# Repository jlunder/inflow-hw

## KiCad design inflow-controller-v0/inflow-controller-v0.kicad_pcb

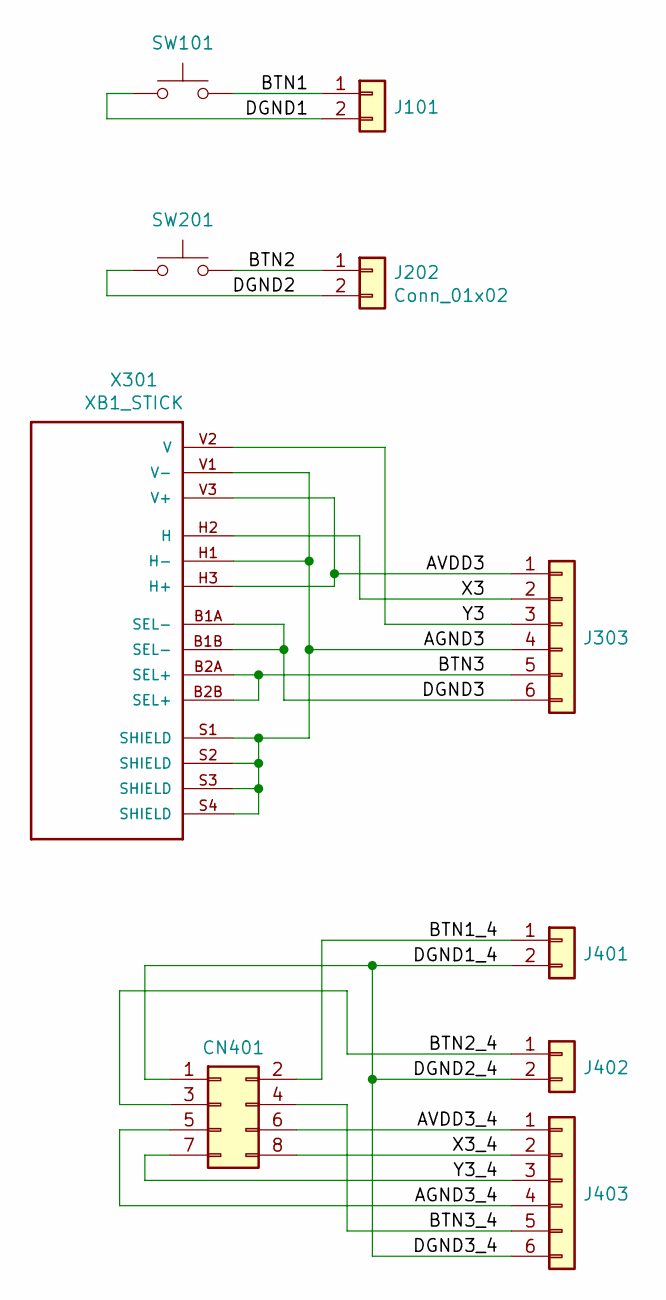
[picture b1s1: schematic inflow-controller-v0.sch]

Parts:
CN401: Conn_02x04_Odd_Even; PinHeader_2x04_P2.54mm_Horizontal
J101, J202, J401, J402: Conn_01x02; PinHeader_1x02_P1.27mm_Vertical
J303, J403: Conn_01x06; PinHeader_1x06_P1.27mm_Vertical
SW101, SW201: SW_Push; SW_SPST_B3S-1000
X301: XB1_STICK; xb1-stick

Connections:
/AGND3: J303.4, X301.H1 (H-), X301.S1 (SHIELD), X301.S2 (SHIELD), X301.S3 (SHIELD), X301.S4 (SHIELD), X301.V1 (V-)
/AGND3_4: CN401.5, J403.4
/AVDD3: J303.1, X301.H3 (H+), X301.V3 (V+)
/AVDD3_4: CN401.6, J403.1
/BTN1: J101.1, SW101.2
/BTN1_4: CN401.2, J401.1
/BTN2: J202.1, SW201.2
/BTN2_4: CN401.3, J402.1
/BTN3: J303.5, X301.B2A (SEL+), X301.B2B (SEL+)
/BTN3_4: CN401.4, J403.5
/DGND1: J101.2, SW101.1
/DGND1_4: CN401.1, J401.2, J402.2, J403.6
/DGND2: J202.2, SW201.1
/DGND3: J303.6, X301.B1A (SEL-), X301.B1B (SEL-)
/X3: J303.2, X301.H2 (H)
/X3_4: CN401.8, J403.2
/Y3: J303.3, X301.V2 (V)
/Y3_4: CN401.7, J403.3

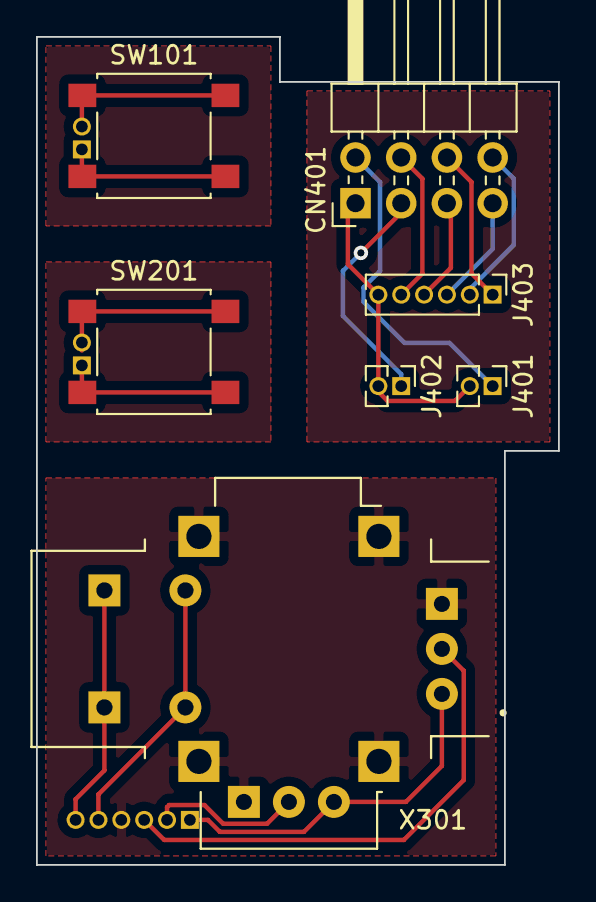
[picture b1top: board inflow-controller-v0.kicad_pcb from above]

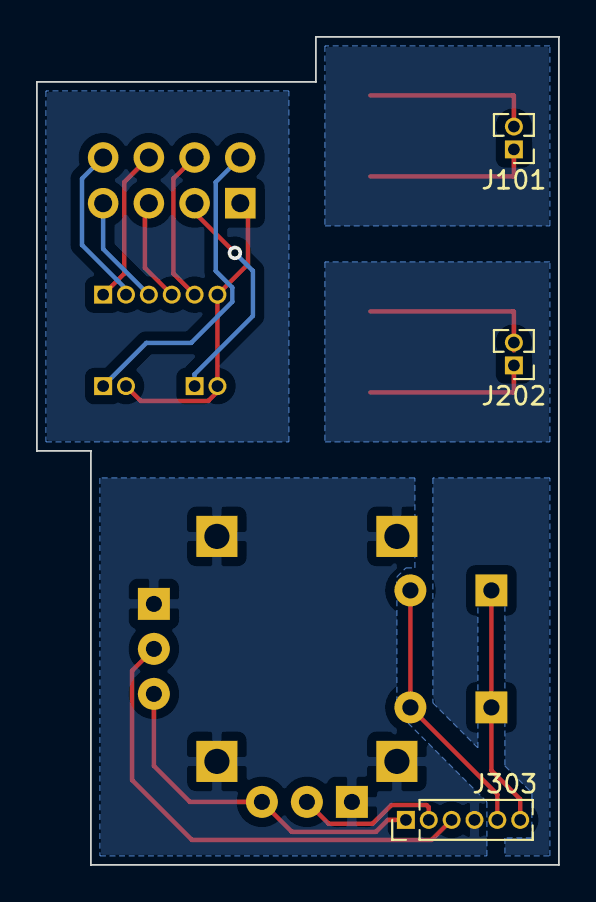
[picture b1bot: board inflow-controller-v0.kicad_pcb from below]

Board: 2 copper layers, 29.0 x 46.0 mm, 10 parts (3 on the bottom side), 18 nets.

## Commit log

2020-09-09 First iteration of schematic
2020-09-21 First pass schematic ready, board a ratsnest still
2020-09-21 Replace joystick component on schematic with SnapEDA symbol and footprint
2020-09-21 Modify analog stick footprint (dimensions seemed to be wrong), route most of the PCBs
2020-11-15 Update xb1-stick joystick footprint and symbol
2020-11-15 Remove accidentally included rescue library
2020-11-16 v0 out for production
2020-11-16 Fix bad silkscreen label positioning
